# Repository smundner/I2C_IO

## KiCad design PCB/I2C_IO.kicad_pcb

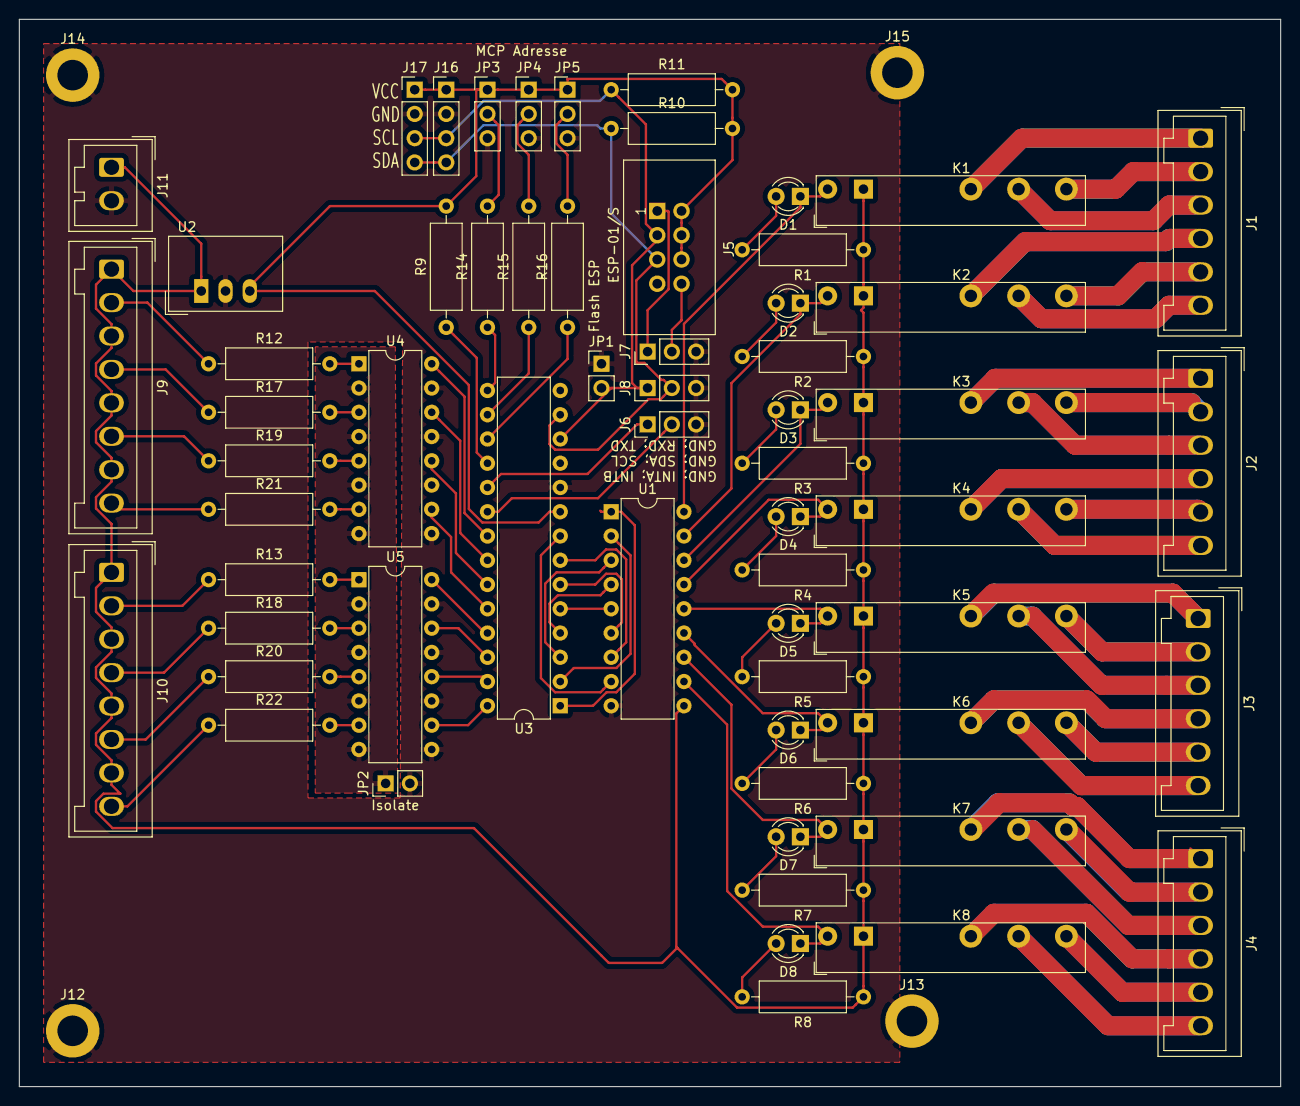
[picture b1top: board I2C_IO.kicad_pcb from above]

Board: 2 copper layers, 132.1 x 111.8 mm, 65 parts (0 on the bottom side), 89 nets.

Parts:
D1, D2, D3, D4, D5, D6, D7, D8: LED; LED_D3.0mm
J1, J2, J3, J4: Conn_01x06; Wago_734-136_1x06_P3.50mm_Vertical
J5: Conn_02x04_Odd_Even; IDC_Header_Straight_8pins
J6, J8: Conn_01x03_Male; PinHeader_1x03_P2.54mm_Vertical
J7: Conn_01x03; PinHeader_1x03_P2.54mm_Vertical
J9, J10: Conn_01x08; Wago_734-138_1x08_P3.50mm_Vertical
J11: Conn_01x02; Wago_734-132_1x02_P3.50mm_Vertical
J12, J13, J14, J15: Conn_01x01; MountingHole_3.2mm_M3_DIN965_Pad
J16, J17: Conn_01x04; PinHeader_1x04_P2.54mm_Vertical
JP1, JP2: Jumper_NO_Small; PinHeader_1x02_P2.54mm_Vertical
JP3, JP4, JP5: Jumper_3_Bridged12; PinHeader_1x03_P2.54mm_Vertical
K1, K2, K3, K4, K5, K6, K7, K8: FINDER-34.51; Relay_SPDT_Finder_34.51_Vertical
R1, R2, R3, R4, R5, R6, R7, R8, R9, R10, R11, R12, R13, R14, R15, R16, R17, R18, R19, R20, R21, R22: R; R_Axial_DIN0309_L9.0mm_D3.2mm_P12.70mm_Horizontal
U1: ULN2801A; DIP-18_W7.62mm
U2: TSR_1-2433; Converter_DCDC_TRACO_TSR-1_THT
U3: MCP23017; DIP-28_W7.62mm
U4, U5: LTV-847M; DIP-16_W7.62mm

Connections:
+12V: J9.1, J9.3, J9.5, J9.7, J10.1, J10.3, J10.5, J10.7, J11.1, K1.A1, K2.A1, K3.A1, K4.A1, K5.A1, K6.A1, K7.A1, K8.A1, R1.1, R2.1, R3.1, R4.1, R5.1, R6.1, R7.1, R8.1, U1.10, U2.1
/INTA: J6.2, U3.20
/INTB: J6.1, U3.19
/In1: U3.21, U4.16
/In2: U3.22, U4.14
/In3: U3.23, U4.12
/In4: U3.24, U4.10
/In5: U3.25, U5.16
/In6: U3.26, U5.14
/In7: U3.27, U5.12
/In8: U3.28, U5.10
/K1-11: J1.3, K1.11
/K1-12: J1.1, K1.12
/K1-14: J1.2, K1.14
/K2-11: J1.6, K2.11
/K2-12: J1.4, K2.12
/K2-14: J1.5, K2.14
/K3-11: J2.3, K3.11
/K3-12: J2.1, K3.12
/K3-14: J2.2, K3.14
/K4-11: J2.6, K4.11
/K4-12: J2.4, K4.12
/K4-14: J2.5, K4.14
/K5-11: J3.3, K5.11
/K5-12: J3.1, K5.12
/K5-14: J3.2, K5.14
/K6-11: J3.6, K6.11
/K6-12: J3.4, K6.12
/K6-14: J3.5, K6.14
/K7-11: J4.3, K7.11
/K7-12: J4.1, K7.12
/K7-14: J4.2, K7.14
/K8-11: J4.6, K8.11
/K8-12: J4.4, K8.12
/K8-14: J4.5, K8.14
/Out1: U1.1, U3.1
/Out2: U1.2, U3.2
/Out3: U1.3, U3.3
/Out4: U1.4, U3.4
/Out5: U1.5, U3.5
/Out6: U1.6, U3.6
/Out7: U1.7, U3.7
/Out8: U1.8, U3.8
/RXD: J5.8, J7.2
/SCL: J5.3, J8.1, J16.3, J17.3, JP1.2, R11.1, U3.12
/SDA: J5.5, J8.2, J16.4, J17.4, R10.1, U3.13
/TXD: J5.1, J7.1
GND: J5.7, J6.3, J7.3, J8.3, J11.2, J12.1, J13.1, J14.1, J15.1, J16.2, J17.2, JP1.1, JP2.2, JP3.3, JP4.3, JP5.3, U1.9, U2.2, U3.10, U4.9, U4.11, U4.13, U4.15, U5.9, U5.11, U5.13, U5.15
GNDA: JP2.1, U4.2, U4.4, U4.6, U4.8, U5.2, U5.4, U5.6, U5.8
unnamed: D1.1, K1.A2, U1.18
unnamed: D1.2, R1.2
unnamed: D2.1, K2.A2, U1.17
unnamed: D2.2, R2.2
unnamed: D3.1, K3.A2, U1.16
unnamed: D3.2, R3.2
unnamed: D4.1, K4.A2, U1.15
unnamed: D4.2, R4.2
unnamed: D5.1, K5.A2, U1.14
unnamed: D5.2, R5.2
unnamed: D6.1, K6.A2, U1.13
unnamed: D6.2, R6.2
unnamed: D7.1, K7.A2, U1.12
unnamed: D7.2, R7.2
unnamed: D8.1, K8.A2, U1.11
unnamed: D8.2, R8.2
unnamed: J9.2, R12.1
unnamed: J9.4, R17.1
unnamed: J9.6, R19.1
unnamed: J9.8, R21.1
unnamed: J10.2, R13.1
unnamed: J10.4, R18.1
unnamed: J10.6, R20.1
unnamed: J10.8, R22.1
unnamed: JP3.2, R14.2
unnamed: JP4.2, R15.2
unnamed: JP5.2, R16.2
unnamed: R9.1, U3.18
unnamed: R12.2, U4.1
unnamed: R13.2, U5.1
unnamed: R14.1, U3.15
unnamed: R15.1, U3.16
unnamed: R16.1, U3.17
unnamed: R17.2, U4.3
unnamed: R18.2, U5.3
unnamed: R19.2, U4.5
unnamed: R20.2, U5.5
unnamed: R21.2, U4.7
unnamed: R22.2, U5.7
VCC: J5.2, J5.4, J5.6, J16.1, J17.1, JP3.1, JP4.1, JP5.1, R9.2, R10.2, R11.2, U2.3, U3.9

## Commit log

2019-10-02 Update Test.ino
    fix read out
2019-10-08 Update Test.ino
    add mqtt to software
2019-10-24 Test programm und abblock kondensatoren
2019-11-11 add case for esp-01 version
